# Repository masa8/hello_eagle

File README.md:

# Hello Eagle
Make your first led circuit with Eagle<br>

## Prerequisite
 OS:Mac  
 
## Install 
Install Eagle
http://www.cadsoftusa.com/download-eagle/

## Make a schematic  
<br>
 Control-Click eagle folder in Projects on Control Panel  
 Select New Project on the context menu  
 Name your project name  
 Control-Click on your project  
 Select New > Schematic  
 Click Add Button   
 Select LED5MM from led > LED  
 Click OK  
 Click once on drawing area  
 Click Stop Button  
 Select R-US_0414/5V from regsistor library  
 Click OK and click drawing area  
 Select GND twice from supply 1 and put it on the area.  
 Select +5V twice from supply 1 and put it on the area.  
 Select WIREPAD1,6/0,8 twice from wirepad and put it on the area.  
 Select MOUNT=HOLES5.0 4 times from holes an put it on the area.  
 Place them as you want   
 Select Wire Button and connect them by  clicking to draw and double-clicking for finishing  
 Click Generate/Swicth To Board Button   
## Make a board
<br>
 Put elements within the area  
 Select AutoRoute Button and Click Continue.. Button  
 Click End Job Button   
 Click Info Button and Click red line on the draweing area  
 Change Width to 0.04  
 Click Grid  
 Change the size to 0.04  
 Select On from Display section  
 Click Rect 
 Click on drawing area to draw 0.08x0.08 Rect.   
 Move them to PAD positions to make it easy to solder.   
 Add text if you want.  
 Save  
## Export Garber Data 
Click excellon.cam from CAM Jobs on Control Panel  
Select File > Open > Board > your board file(.brd) saved above.  
Click Process Job  
Click x button  
Click gerb274x[2L].cam  (or any you want)  
Select File > Open > Board > your board file(.brd) saved above.  
Click Process Job  

### (Option) Garber File Format: Replace \n with \r\n  
If your export files need to be used on Windows  
I do just like following:  
brew install unix2dos  
cd [your project folder]  
ls | grep [your project name] | xargs unix2dos  
od -c [a your file name]  for checking there is \r in your file.  
 
## c.f.
* gerb274x[2L].com http://www.p-ban.com/gerber/eagle.html

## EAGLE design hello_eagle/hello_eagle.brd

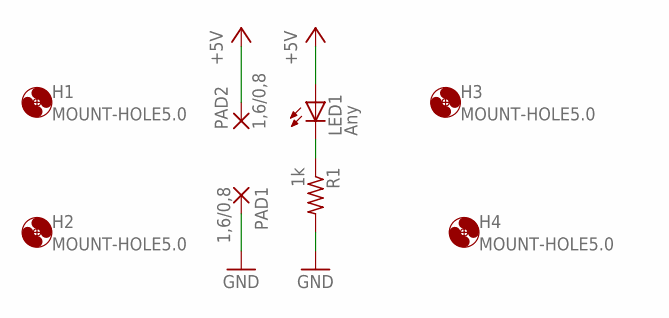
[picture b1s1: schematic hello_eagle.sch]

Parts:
H1, H2, H3, H4: MOUNT-HOLE5.0; 5,0
LED1: Any; LED5MM
PAD1, PAD2: 1,6/0,8
R1: 1k; 0414V

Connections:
+5V: LED1.A, PAD2.1
GND: PAD1.1, R1.2
unnamed: LED1.K (C), R1.1

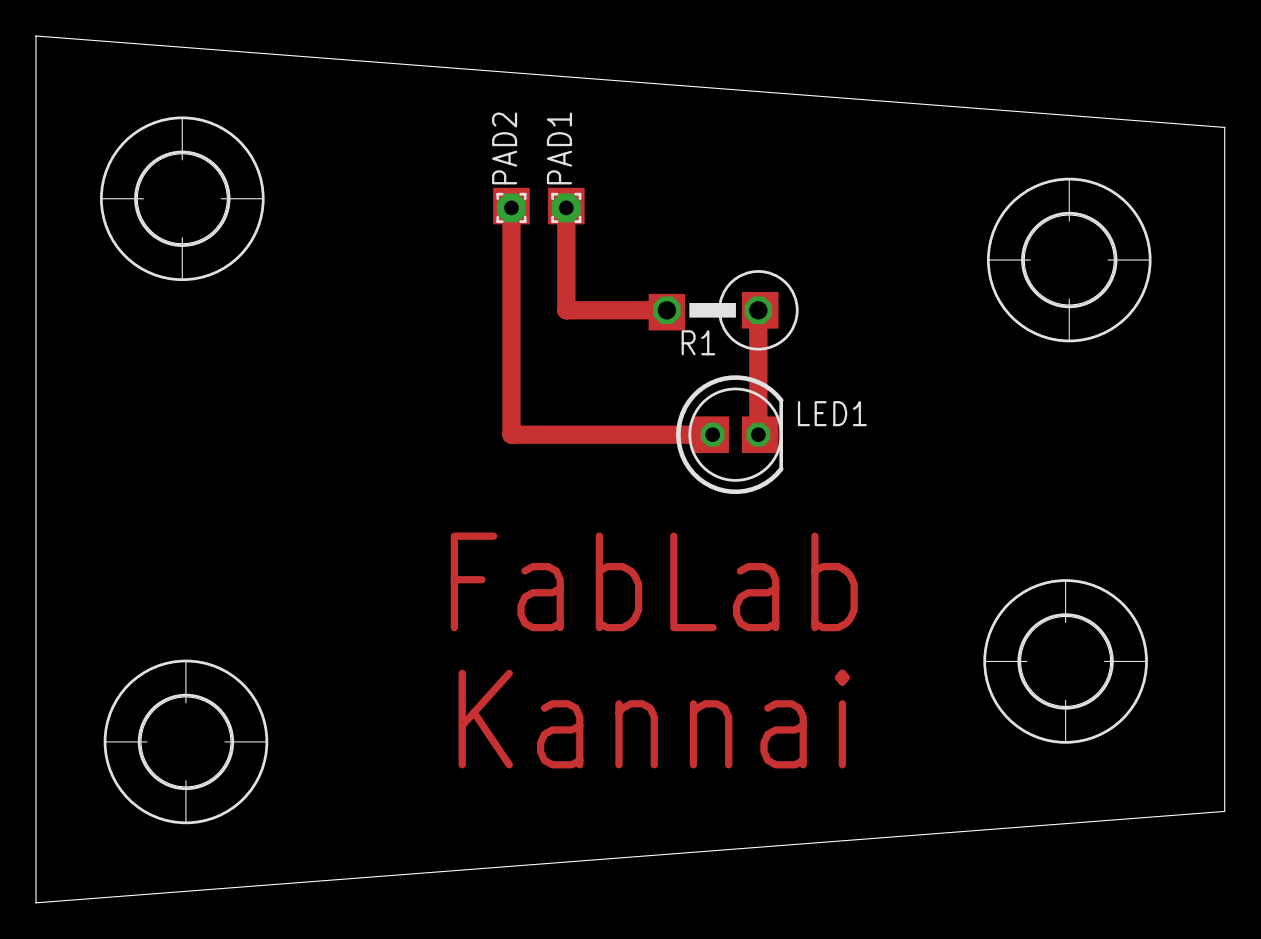
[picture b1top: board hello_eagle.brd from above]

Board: 2 copper layers, 66.0 x 48.2 mm, 8 parts (0 on the bottom side), 3 nets.

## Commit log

2015-07-04 first eagle data
2015-07-05 Add ignorefile
2015-07-05 Add images
2015-07-05 change directory name
2015-07-05 README.md
2015-07-05 change to img tag
2015-07-05 Append desc
